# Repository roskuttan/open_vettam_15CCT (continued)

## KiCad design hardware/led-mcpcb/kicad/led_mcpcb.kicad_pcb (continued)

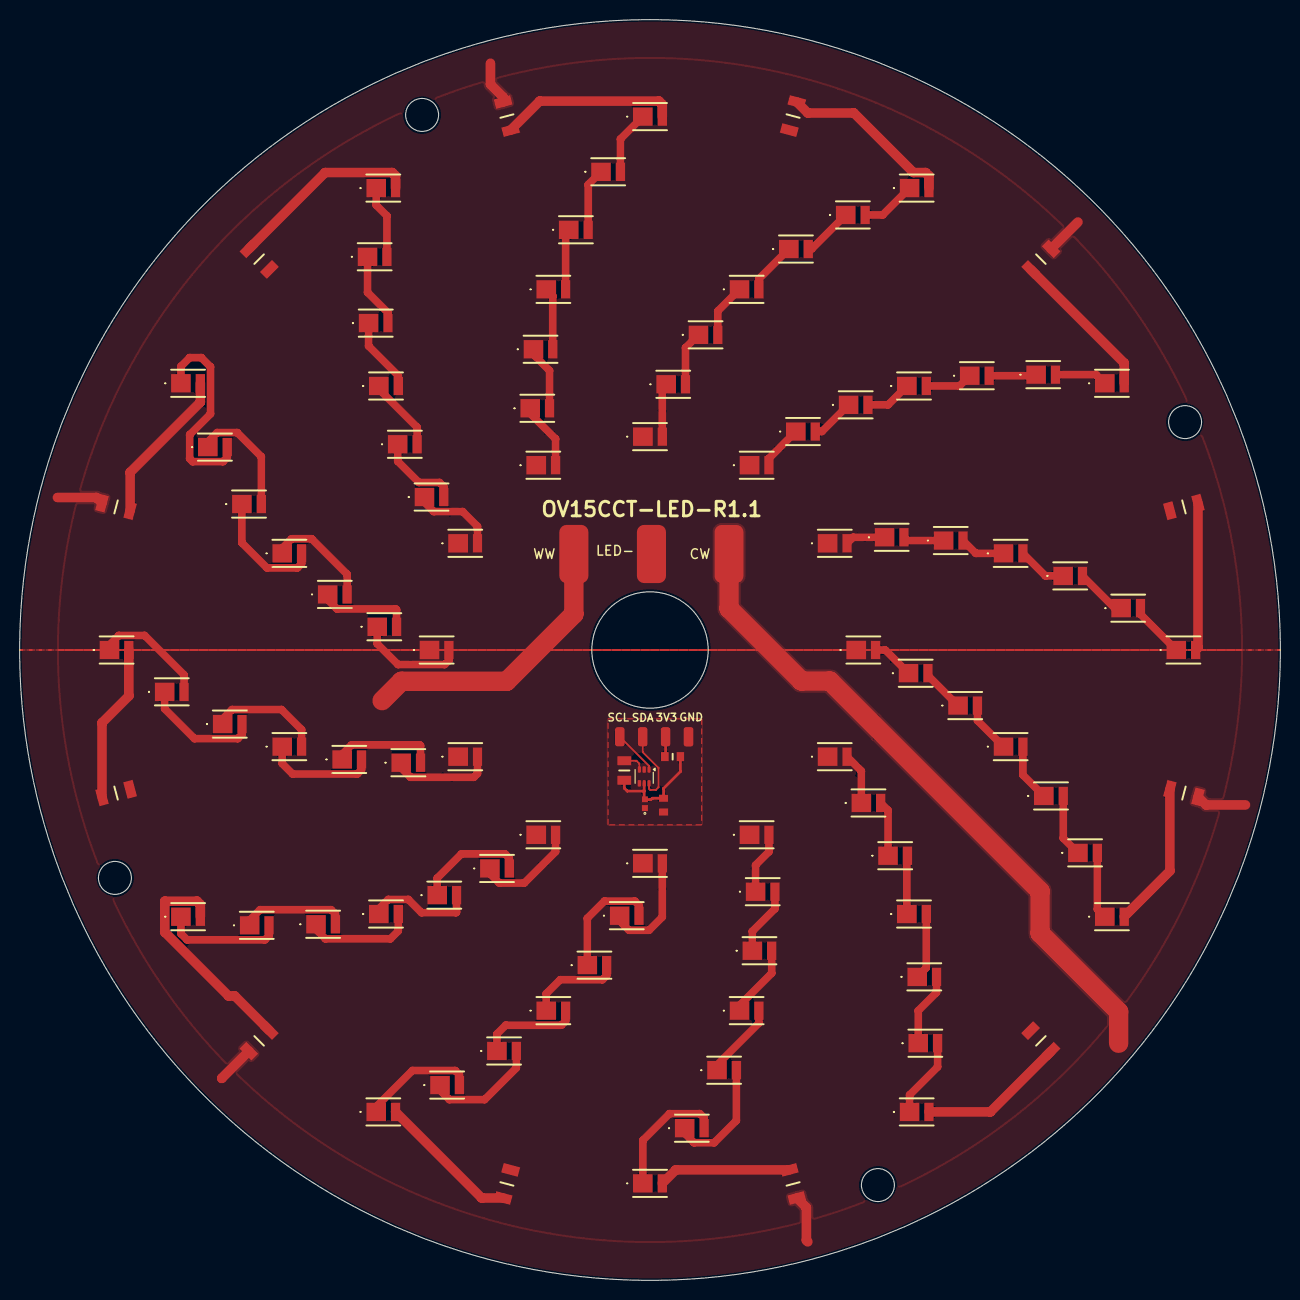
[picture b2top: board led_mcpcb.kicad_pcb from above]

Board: 2 copper layers, 130.0 x 130.0 mm, 108 parts (0 on the bottom side), 93 nets.

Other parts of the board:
CW: CW+; SolderWirePad_1x01_SMD_3x6mm
LED-: LED-; SolderWirePad_1x01_SMD_3x6mm
WW: WW+; SolderWirePad_1x01_SMD_3x6mm

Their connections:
GND0: LED-.1 (Pin_1_1); also elsewhere on the board
unnamed 9: CW.1 (Pin_1_1); also elsewhere on the board
unnamed 10: WW.1 (Pin_1_1); also elsewhere on the board

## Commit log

2026-04-18 Rename project to open_vettam_15CCT
2026-05-05 Finalize KiCad PCB sources for 5-piece test build
    Commit the completed Open Vettam 15CCT KiCad source design files prepared for the initial five-piece production test run.
    Included files are limited to the schematic hierarchy, PCB layouts, KiCad project files, and the LED MCPCB design-rules file. Generated BOM exports, fabrication output archives, freerouting/temp file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
    Updated main controller board sources:
    - open_vettam_15CCT.kicad_sch
    - open_vettam_15CCT.kicad_pcb
    - open_vettam_15CCT.kicad_pro
2026-06-15 Update LED MCPCB pads and shared LED return
    Reduce LED pin pad sizes for easier soldering and remove unnecessary pad area.
    Replace separate WW- and CW- connections with one shared LED- common connection for the planned common-connection driver IC.
    Organize the updated hardware source and manufacturing files under hardware/.
2026-06-15 Document verified hardware specifications and interfaces
